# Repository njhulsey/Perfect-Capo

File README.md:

# Perfect-Capo
The electrical system of perfect-capo is capable of unclenching the clamp mechanism via capacitive touch. The board uses an ATtiny84 MCU for basic logic and control. It is capable of driving the speed and direction of a DC Motor via an H-bridge. The pins along the edge of the PCB are for external connections to be soldered on (such as Motor, Capacitive touch, Battery, Switch). The entire system is powered by a 3.7v LiPo Battery which is buck-boosted to 5v for better motor performance. A Micro-USB connector is present for programming and battery charging. The MCU uses a bootloader to simulate USB for simple hardware implementation. It is also able to charge the LiPo via the MCP73831 IC. Many additional pinouts are available for easy hackability and ease of use.

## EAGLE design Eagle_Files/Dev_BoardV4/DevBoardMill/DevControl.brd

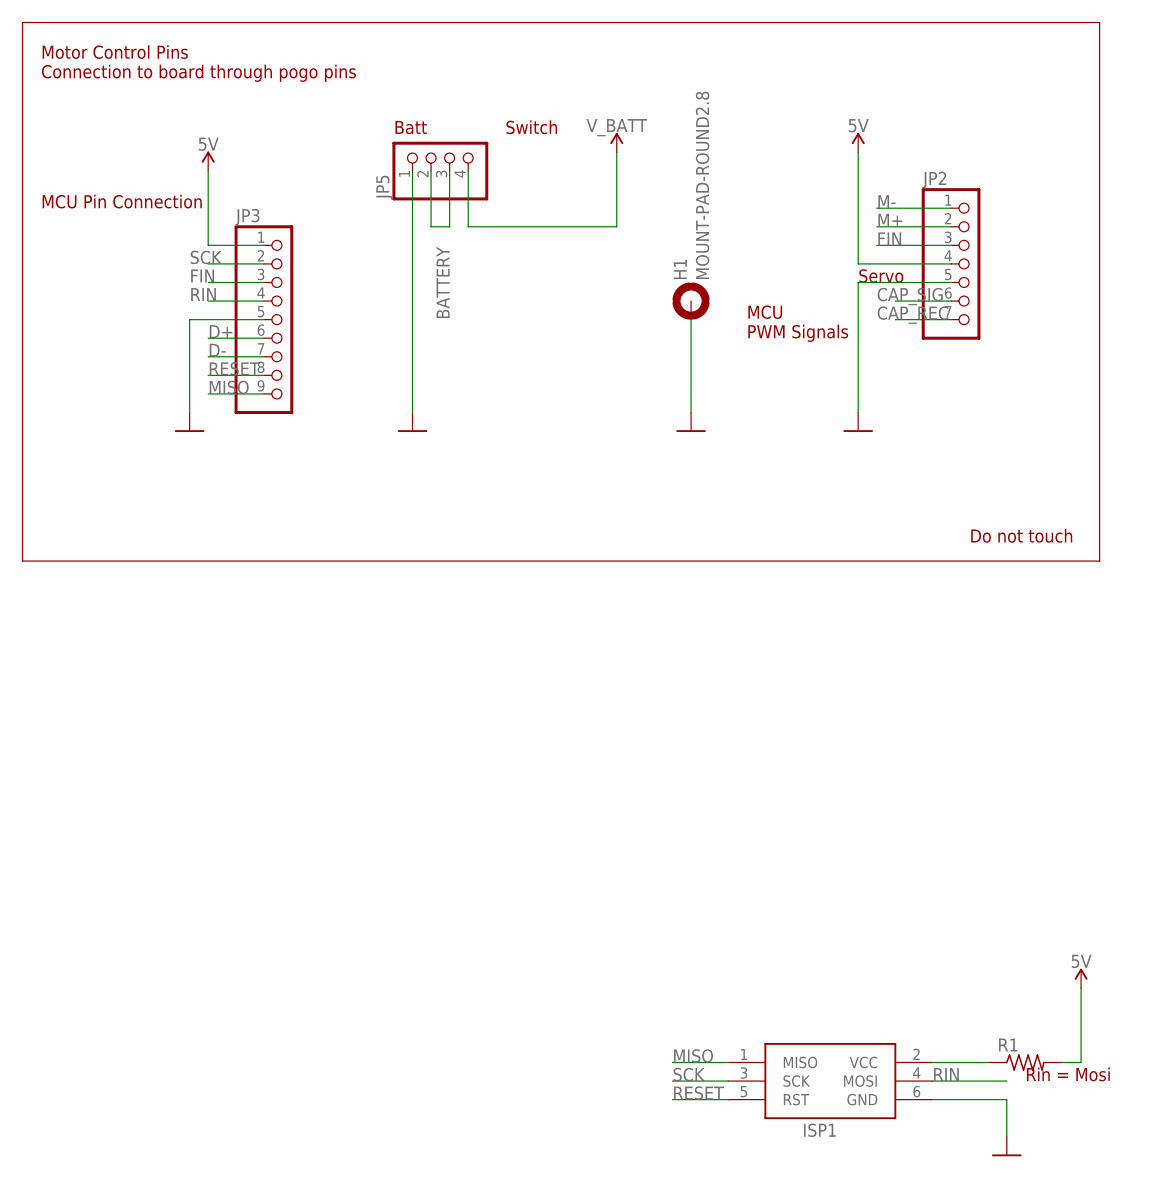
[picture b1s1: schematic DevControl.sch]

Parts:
H1: MOUNT-PAD-ROUND2.8; 2,8-PAD
ISP1: AVRISP-6; AVRISP
JP2: HEADER-1X7; 1X07_OVAL
JP3: HEADER-1X9; 1X09_OVAL
JP5: HEADER-1X4; 1X04_OVAL
R1: R-US_R0805; R0805

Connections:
5V: JP2.4, JP3.1, R1.2
BATTERY: JP5.2, JP5.3
CAP_REC: JP2.7
CAP_SIG: JP2.6
D+: JP3.6
D-: JP3.7
FIN: JP2.3, JP3.3
GND: H1.B2,8, ISP1.6 (GND), JP2.5, JP3.5, JP5.1
M+: JP2.2
M-: JP2.1
MISO: ISP1.1 (MISO), JP3.9
unnamed: ISP1.2 (VCC), R1.1
RESET: ISP1.5 (RST), JP3.8
RIN: ISP1.4 (MOSI), JP3.4
SCK: ISP1.3 (SCK), JP3.2
V_BATT: JP5.4

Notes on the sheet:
MCU PWM Signals
Batt
Switch
MCU Pin Connection
Servo
Motor Control Pins Connection to board through pogo pins
Do not touch
Rin = Mosi

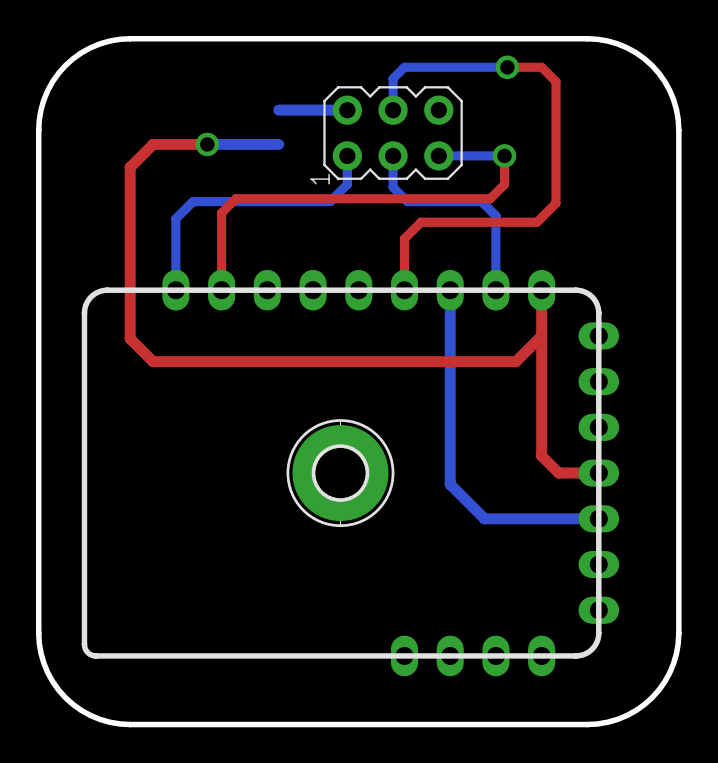
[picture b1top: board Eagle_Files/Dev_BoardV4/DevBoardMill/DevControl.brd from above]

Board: 2 copper layers, 35.6 x 38.1 mm, 6 parts (1 on the bottom side), 9 nets.

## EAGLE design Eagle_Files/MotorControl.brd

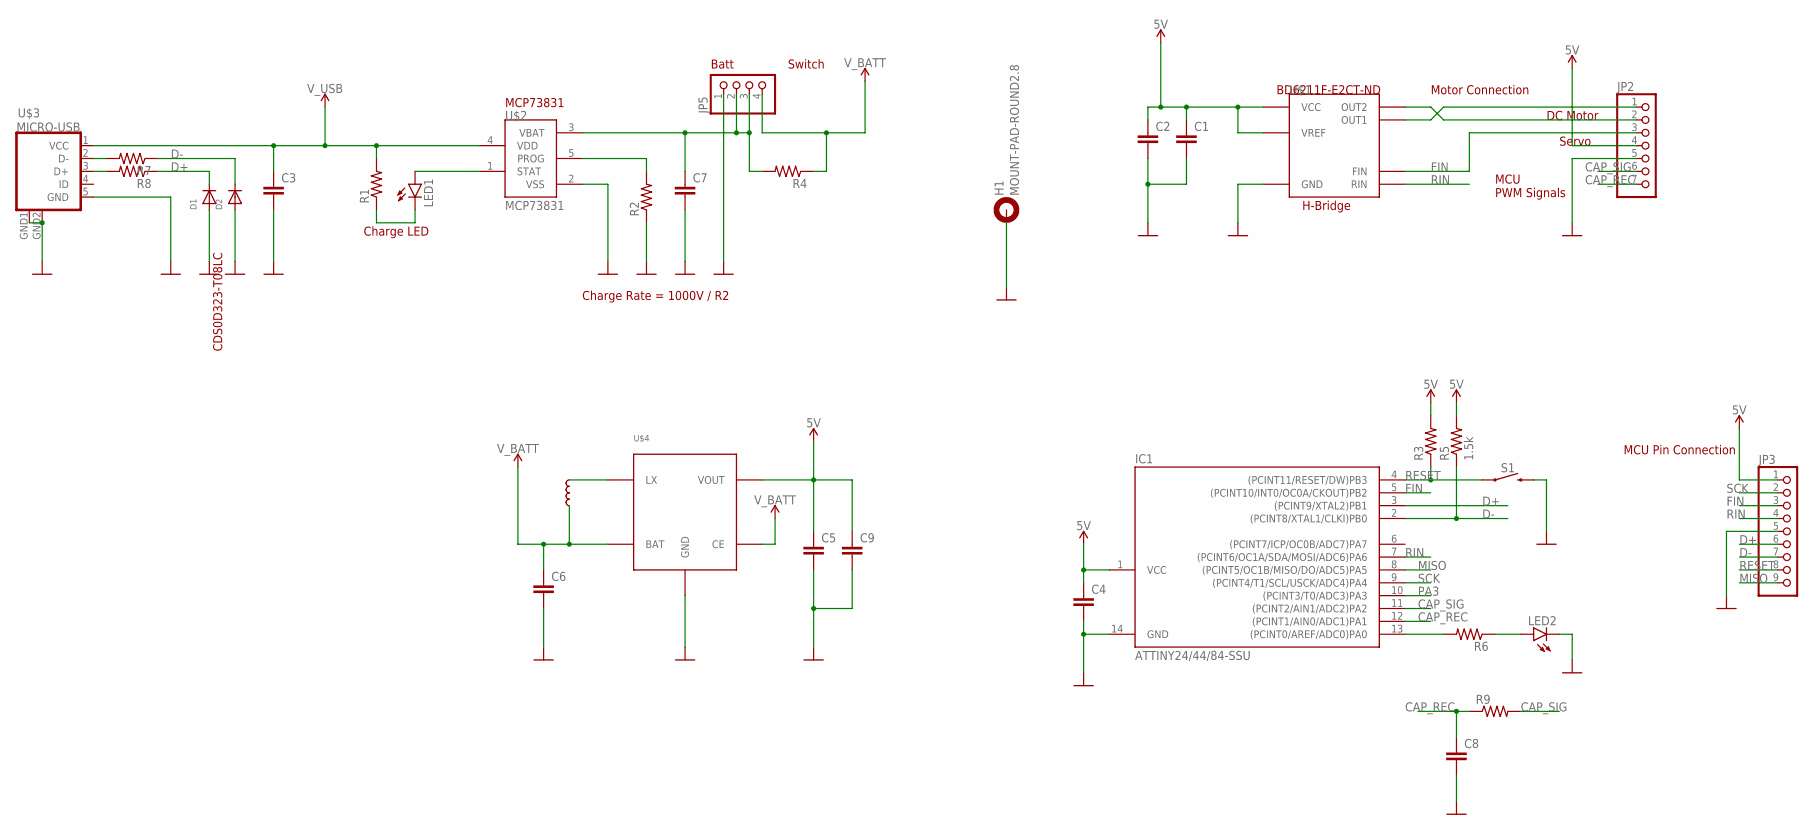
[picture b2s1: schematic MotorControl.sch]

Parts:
C1, C2, C3, C4, C5, C6, C7, C8, C9: C-EUC0603; C0603
D1, D2: DIODESOD-323; SOD-323
H1: MOUNT-PAD-ROUND2.8; 2,8-PAD
IC1: ATTINY24/44/84-SSU; SOIC14
JP2: HEADER-1X7; 1X07_OVAL
JP3: HEADER-1X9; 1X09_OVAL
JP5: HEADER-1X4; 1X04_OVAL
LED1, LED2: LEDCHIP-LED0805; CHIP-LED0805
R1, R2, R3, R4, R6, R7, R8, R9: R-US_R0603; R0603
R5: 1.5k; R0603
S1: MOMENTARY-SWITCH-SPST-SMD-5.2MM; TACTILE_SWITCH_SMD_5.2MM
U$1: H-BRIDGE-BD6210F; 8-SOP
U$2: MCP73831; SOT23-5L
U$3: MICRO-USB
U$4: XC9141B50C; SOT-25
U$5: INDUCTOR; SMD_INDUCTOR

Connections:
5V: C1.1, C2.1, C4.1, C5.1, C9.1, IC1.1 (VCC), JP2.4, JP3.1, R3.2, R5.2, U$1.P$2 (VCC), U$1.P$3 (VCC), U$1.P$6 (VREF), U$4.P$4 (VOUT)
CAP_REC: C8.1, IC1.12 ((PCINT1/AIN0/ADC1)PA1), JP2.7, R9.1
CAP_SIG: IC1.11 ((PCINT2/AIN1/ADC2)PA2), JP2.6, R9.2
D+: D1.C, IC1.3 ((PCINT9/XTAL2)PB1), JP3.6, R8.1
D-: D2.C, IC1.2 ((PCINT8/XTAL1/CLKI)PB0), JP3.7, R5.1, R7.1
FIN: IC1.5 ((PCINT10/INT0/OC0A/CKOUT)PB2), JP2.3, JP3.3, U$1.P$4 (FIN)
GND: C1.2, C2.2, C3.2, C4.2, C5.2, C6.2, C7.2, C8.2, C9.2, D1.A, D2.A, H1.B2,8, IC1.14 (GND), JP2.5, JP3.5, JP5.1, LED2.C, R2.1, S1.3 (2), U$1.P$8 (GND), U$2.2 (VSS), U$3.5 (GND), U$3.GND1 (GND), U$3.GND2 (GND), U$4.P$2 (GND)
MISO: IC1.8 ((PCINT5/OC1B/MISO/DO/ADC5)PA5), JP3.9
unnamed: LED2.A, R6.1
unnamed: R7.2, U$3.2 (D-)
unnamed: LED1.C, R1.1
unnamed: LED1.A, U$2.1 (STAT)
unnamed: JP2.1, U$1.P$1 (OUT1)
unnamed: JP2.2, U$1.P$7 (OUT2)
unnamed: R8.2, U$3.3 (D+)
unnamed: IC1.13 ((PCINT0/AREF/ADC0)PA0), R6.2
unnamed: R2.2, U$2.5 (PROG)
unnamed: C7.1, JP5.2, JP5.3, R4.2, U$2.3 (VBAT)
unnamed: U$4.P$5 (LX), U$5.P$2
PA3: IC1.10 ((PCINT3/T0/ADC3)PA3)
RESET: IC1.4 ((PCINT11/RESET/DW)PB3), JP3.8, R3.1, S1.1
RIN: IC1.7 ((PCINT6/OC1A/SDA/MOSI/ADC6)PA6), JP3.4, U$1.P$5 (RIN)
SCK: IC1.9 ((PCINT4/T1/SCL/USCK/ADC4)PA4), JP3.2
V_BATT: C6.1, JP5.4, R4.1, U$4.P$1 (CE), U$4.P$3 (BAT), U$5.P$1
V_USB: C3.1, R1.2, U$2.4 (VDD), U$3.1 (VCC)

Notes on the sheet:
MCU PWM Signals
Motor Connection
BD6211F-E2CT-ND
MCP73831
Batt
Switch
Charge LED
Charge Rate = 1000V / R2
H-Bridge
MCU Pin Connection
DC Motor
Servo
CDS0D323-T08LC

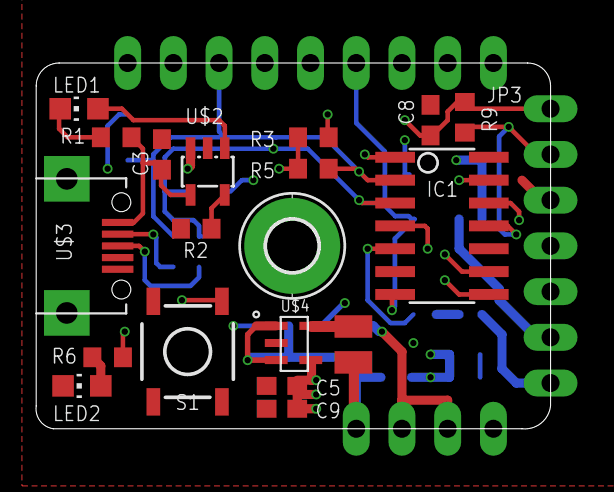
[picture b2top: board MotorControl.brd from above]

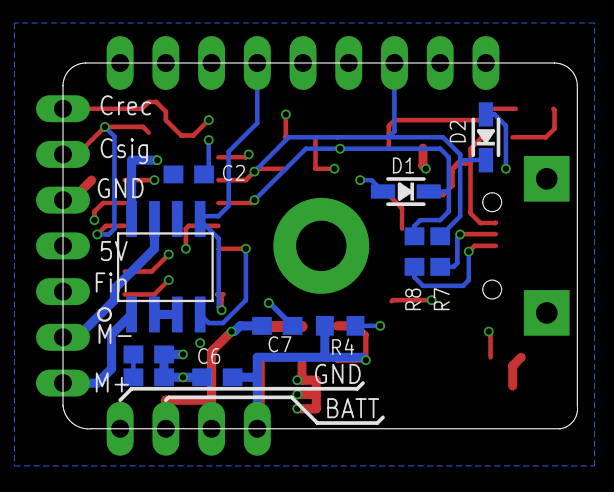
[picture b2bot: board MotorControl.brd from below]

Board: 4 copper layers, 28.6 x 20.3 mm, 33 parts (11 on the bottom side), 24 nets.

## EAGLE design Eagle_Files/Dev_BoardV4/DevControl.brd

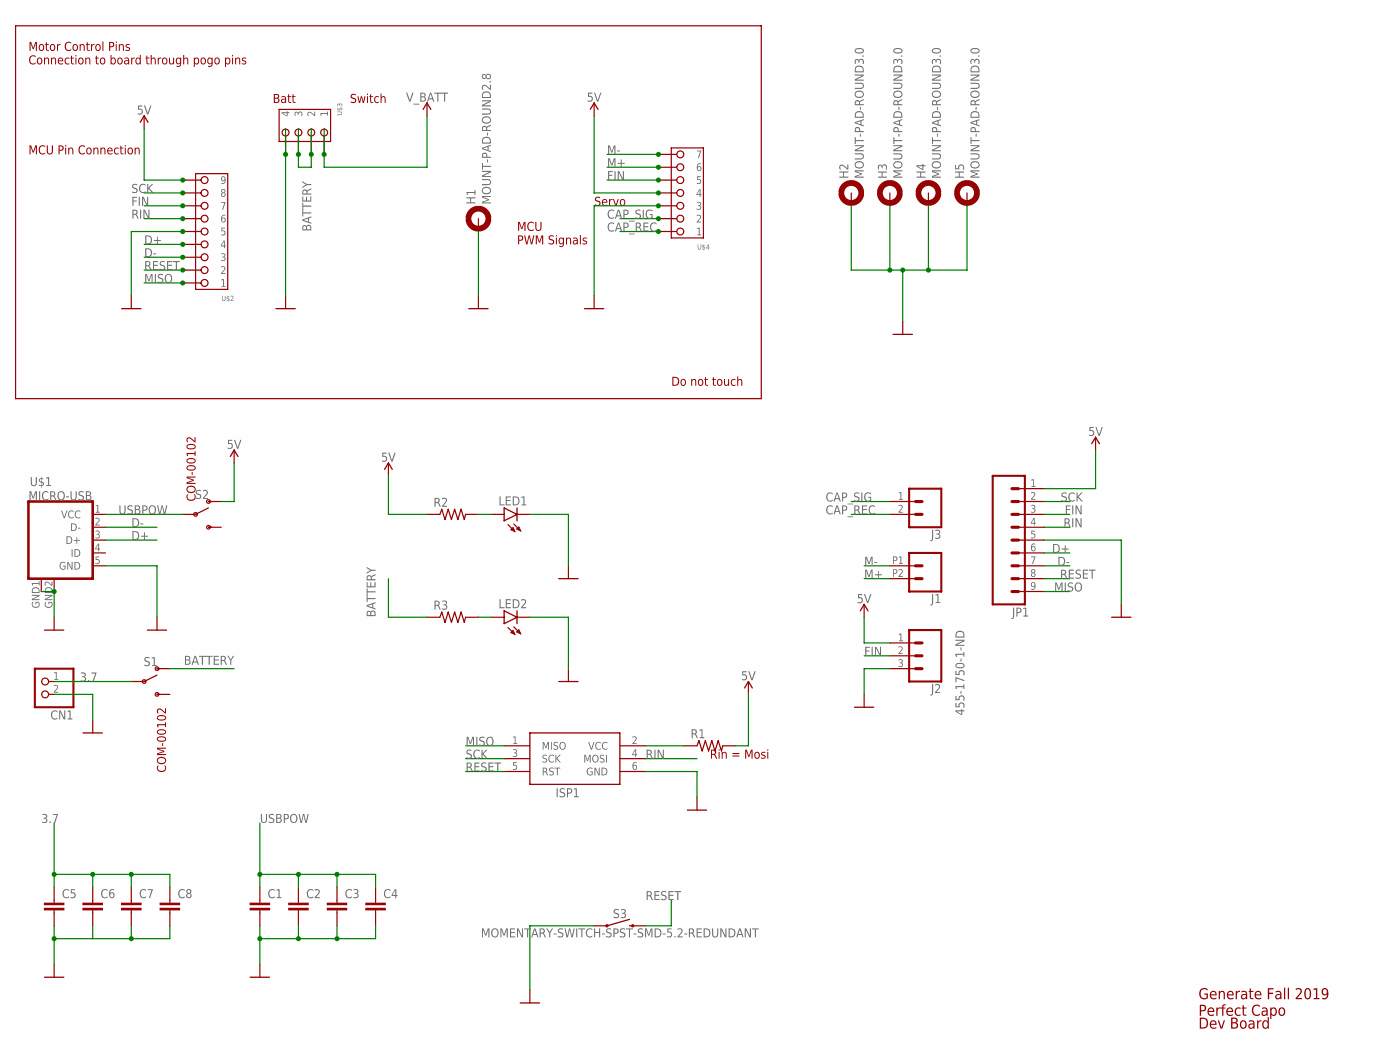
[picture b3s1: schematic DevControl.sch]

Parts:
C1, C2, C3, C4, C5, C6, C7, C8: C-EUC0805; C0805
CN1: JST_2PIN-SMT-RA; JST-PH-2-SMT-RA
H1: MOUNT-PAD-ROUND2.8; 2,8-PAD
H2, H3, H4, H5: MOUNT-PAD-ROUND3.0; 3,0-PAD
ISP1: AVRISP-6; AVRISP
J1: CONN_022.54MM_SCREWTERM; 1X02_2.54_SCREWTERM
J2: 455-1750-1-ND; 1X03
J3: CONN_02; 1X02
JP1: CONN_09; 1X09
LED1, LED2: LEDCHIPLED_0805; CHIPLED_0805
R1, R2, R3: R-US_R0805; R0805
S1, S2: SWITCH-SPDT-PTH-11.6X4.0MM; SWITCH_SPDT_PTH_11.6X4.0MM
S3: MOMENTARY-SWITCH-SPST-SMD-5.2-REDUNDANT; TACTILE_SWITCH_SMD_5.2MM
U$1: MICRO-USB
U$2: POGO-1X9
U$3: POGO-1X4
U$4: POGO-1X7

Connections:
3.7: C5.1, C6.1, C7.1, C8.1, CN1.1 (2), S1.2
5V: J2.1, JP1.1, R1.2, R2.1, S2.1 (O), U$2.P$9 (9), U$4.P$4 (4)
BATTERY: R3.1, S1.1 (O), U$3.P$2 (2), U$3.P$3 (3)
CAP_REC: J3.2, U$4.P$1 (1)
CAP_SIG: J3.1, U$4.P$2 (2)
D+: JP1.6, U$1.3 (D+), U$2.P$4 (4)
D-: JP1.7, U$1.2 (D-), U$2.P$3 (3)
FIN: J2.2, JP1.3, U$2.P$7 (7), U$4.P$5 (5)
GND: C1.2, C2.2, C3.2, C4.2, C5.2, C6.2, C7.2, C8.2, CN1.2 (1), H1.B2,8, H2.B3,0, H3.B3,0, H4.B3,0, H5.B3,0, ISP1.6 (GND), J2.3, JP1.5, LED1.C, LED2.C, S3.1, S3.2 (1), U$1.5 (GND), U$1.GND1 (GND), U$1.GND2 (GND), U$2.P$5 (5), U$3.P$4 (4), U$4.P$3 (3)
M+: J1.P2 (2), U$4.P$6 (6)
M-: J1.P1 (1), U$4.P$7 (7)
MISO: ISP1.1 (MISO), JP1.9, U$2.P$1 (1)
unnamed: ISP1.2 (VCC), R1.1
unnamed: LED1.A, R2.2
unnamed: LED2.A, R3.2
RESET: ISP1.5 (RST), JP1.8, S3.3 (2), S3.4 (2), U$2.P$2 (2)
RIN: ISP1.4 (MOSI), JP1.4, U$2.P$6 (6)
SCK: ISP1.3 (SCK), JP1.2, U$2.P$8 (8)
USBPOW: C1.1, C2.1, C3.1, C4.1, S2.2, U$1.1 (VCC)
V_BATT: U$3.P$1 (1)

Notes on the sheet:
MCU PWM Signals
Batt
Switch
MCU Pin Connection
Servo
Motor Control Pins Connection to board through pogo pins
Do not touch
Rin = Mosi
Generate Fall 2019 Perfect Capo
Dev Board
COM-00102

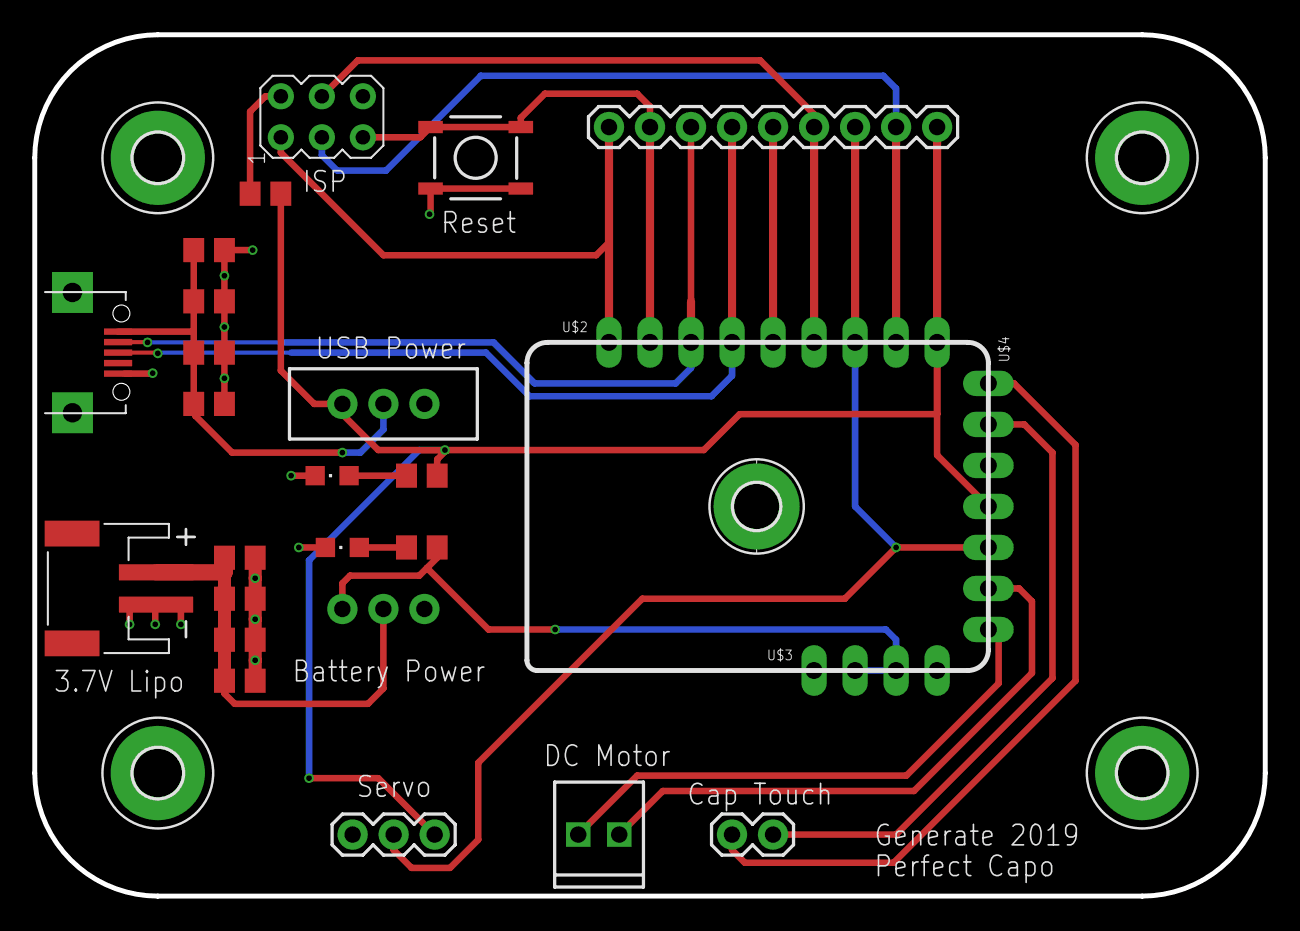
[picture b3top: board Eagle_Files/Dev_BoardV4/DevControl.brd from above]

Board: 2 copper layers, 76.2 x 53.3 mm, 31 parts (1 on the bottom side), 19 nets.

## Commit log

2019-12-30 Create EagleFiles

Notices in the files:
parts and their libraries:
microbuilder: This work is placed in the public domain, and may be freely used for commercial and non-commercial work with the following conditions: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
SparkFun-PowerSymbols: Licensing: Creative Commons ShareAlike 4.0 International - https://creativecommons.org/licenses/by-sa/4.0
